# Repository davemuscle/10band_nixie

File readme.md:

# IN-9 Nixie Tube Spectrum Analyzer - Analog

*Migrated to Git on February 20th, 2022. Original release July 5th, 2020.*

I've been interested in doing a project with IN-9 Nixie Tubes for some time, and with the
manufacturing for these "old world" displays having been discontinued for decades now, it definitely
feels special to work with these devices. IN-9s are glass tubes filled with Neon or Argon gas, and
when driven by 150V and a low current is sunk through them, the tube lights up and looks nice. I
picked up 25 IN-9 Nixie Tubes for $130 from a Ukrainian seller on Ebay for this and future projects.

It seemed like these tubes just wanted to be used for a 10-band spectrum analyzer, so I decided to
make it completely analog to switch things up. It was fun building the filters, peak detectors, and
boost converter, and I'm happy with the result; but the next projects will be going back to digital,
for sure.

The general timeframe of this project was between mid-April to the end of May 2020. I also
redesigned the website at the start of July.

## Demonstration
CTRL+click the video thumbnails to open in a new tab

| Youtube Videos |
| :--: |
| *IN-9 Nixie Tube 10-Band Spectrum Analyzer - Demo* |
|  |
| *IN-9 Nixie Tube 10-Band Spectrum Analyzer - OSRS Lunar Isle* |
|  |

## Implementation

### Tube Operation

The general operation of the IN-9 is pretty simple, as there are only two pins to work with. When a
striking voltage of ~150V is placed on the anode of the device, the Neon / Argon gas in the tube
becomes ionized, converting it into plasma.

When a current is then sunk through the tube, the plasma sputters against the cathode to produce the
glow. The height of the glow is linearlly proportional to the current through the tube, up to 10 mA.
After that the glow just gets brighter.

### Tube Circuitry

The circuit I used to drive each IN-9 tube was a simple NPN current sink. The only hard part in
using these tubes is getting your hands on +150V. The power circuit is shown later in the
"Schematic" section.

In the circuit below, R1 and Vb control the current through the tube. 

Any NPN can be used as long as the Collector-Emmitter breakdown voltage is reasonably higher than
the striking voltage. I used an MJE340, which has a breakdown of 300V (double my striking voltage).

### Tube Burn-In

Each Nixie has to go through a "burn-in" process. This process is just driving the tube at a higher
current for any amount of time. To burn my tubes in I lowered R1 in the circuit above. Shown below
is a 4x speedup of a tube being slowly burned in.

Most of the tubes available for purchase are NOS: "new-old stock", meaning they are old but unused.
They need to be burned in because they've been sitting in a warehouse in Russia for 30 years!

Burn in can also fix issues related to cathode poisoning, which is the build-up of deposited metal
on the cathode from the sputtering mentioned earlier. Cathode poisoning can cause tubes to stop
working or be less visible.

### Tube Failures

The reliability of the tubes is definitely not a buying point. Out of the 15 I tested, 2 of them
wouldn't work correctly and 1 of them mysteriously stopped working.

The picture above was me trying to reburn-in the tube that had stopped working. That white
light highlited in red isn't from a camera; it's some failure by the tube. Either the neon wasn't
ionizing, this was cathode poisoning, or something else. 

You'll also notice in the demo videos that the right-most tube doesn't display correctly, which is
fine. 

## Schematic

[Download a PDF of the schematic here](/doc/NixieAnalyzer.pdf)

### Power

The Nixie Tubes are powered buy 12V boosted up to 150V using the MC34063 switching controller (for
an SMPS). This is an old, cheap, simple chip that can act as a boost / buck converter, or as a
voltage inverter. It works by adjusting the switching duty-cycle out of pin 2 to regulate a constant
output voltage. In my configuration, 12V gets boosted up to ~75V through Q2, L1 and C10. The
capacitor network on the output acts as a doubler, giving me ~150V.

I was actually able to build this SMPS on a breadboard, but make sure to pay attention to your
wiring if you decide to. I had to build it a few times to get it right. The only issue I experienced
was the voltage dropout on the load. With 5 tubes on at full height, the voltage dropped to about
~130V. This was because the MC34063 only has a max duty cycle of 85%; a modern chip with better
efficiency probably wouldn't have dropped out. 

Check the references for the source for this circuit.

I used the L7805 regulator to convert 12V to 5V for powering the OpAmps / other ICs.

### Audio Front End

The audio layer is just an input and output jack and an inverting amplifier. I like to make my
spectrum analyzer's not change the volume of the sound, so I just did a loopback here. The sound is
split from stereo to mono via R26 and R27, and is passed through an inverting amplifier. RV2 can be
turned to give a gain between 1 and 18. When soldering the circuit I used 300ohms for R31 and R34
since I wanted more gain.

Since I used a single-supply setup for my board, I had to generate a 2.5V bias using R32, R33, and
U7B. 

### State Variable Filter, Peak Detector, Current Sink (repeat 10x)

The bandpass filter topology I went with was the State Variable Filter. It's a good topology since
you only need to swap out two resistors, R13 and R15, to get a different center frequency. R6, R7,
and R9 control the gain and Q-factor, which I just played with to get right. R11 and R12 I picked 1K
and never had to change it. I believe those resistors cancel out in the reduced equations. 

Another good reason to use the State Variable Filter is that you also get lowpass and highpass
outputs. The highpass output is on pin 7, and the lowpass is on pin 14 of U3.

After filtering the sound through the bandpass filter, I convert it to DC via the peak detector at
U4. We have now effectively taken an FFT.

The DC peak then goes through a jumper and into the base of the NPN current sink. The jumper allows
for switching between burning the tube in or normal operation.

### Tube Driver

I extended the NPN current sink by adding an additional transistor at the emitter of the MJE340.
This transistor was driven by a pulse, about 100 Hz, making the current through the tube be pulsed.
This is required for using IN-9 tubes, otherwise they will not operate correctly: sometimes the glow
will start in the middle, or maybe the glow will extend from the top-down. The IN-13's tried to fix
this by adding an auxilliary cathode pin, but I'm not sure how well that works.

U6 is the common 555 timer, used to generate the 100 Hz pulse. You can use any frequency above the
persistence of version (see the references), I found 100 Hz to work well. D6 is used to get as close
to 50% duty cycle as possible.

The output of the 555 timer is then inverted via Q4, to give me two square waves (TubeClockA,
TubeClockB) with a 180 degree phase difference. TubeClockA enables to 5 tubes, and TubeClockB
enables 5 tubes, each at different times. This relaxes my power supply current by only having to
power 5 tubes at once. But, since the tubes are actually being flickered at 100 Hz, we perceive 10
of them as constantly on.

RV1 is a trim potentiometer used to vary the burn-in voltage. For my circuit, 3-4V was pretty good.

## Layout

The general layout is: audio layer and tube driver on the left, filters in the middle, power on the
right.

The bottom part of the PCB with the holes snaps off and fits on top of the main board. Rubber
grommets are inserted into the holes, the nixie tubes are pushed in, and their leads are snapped
into the screw terminals. I wanted a setup like this so I didn't have to solder any tubes onto the
board. Each tube can be easily swapped if there is a failure.

I included an extra two snap-off Nixie holders for future projects. The rubber grommets that
perfectly fit the IN-9s I used are the "742" from Keystone Electronics. They have a inner diameter
of 0.312", a panel thickness of 0.062", a cutout of 0.437", and a total diameter of 0.625". I had to
try a bunch of different grommets until I found the right one, so hopefully this is helpful.

## Improvements

A smarter way to do this would have been with a switched-capacitor filter, which would have reduced
soldering time and component count. I would remove the 32 Hz and 16 kHz bands, since those tubes are
hardly used compared to the others. I would also use a higher voltage than 5V for the main power
rail. Using 5V limited my headroom and dynamic range.

## References
1. [Wikipedia, Nixie Tubes](https://en.wikipedia.org/wiki/Nixie_tube)
2. [Wikipedia, Plasma](https://en.wikipedia.org/wiki/Plasma_physics)
3. [Wikipedia, Ionization](https://en.wikipedia.org/wiki/Ionization)
4. [Wikipedia, Sputtering](https://en.wikipedia.org/wiki/Sputtering)
5. [Threeneuron's, Nixie Power Supply](https://threeneurons.wordpress.com/nixie-power-supply/)
6. [SaltEChips, Theory of operation and construction of the IN-13 nixie gas-discharge
   tube](https://www.saltechips.com/lab/theory-of-operation-and-construction-of-the-in-13-nixie-gas-discharge-tube/)
7. [Dieter's Nixie-Tube Pages, Tutorial: Cathode Poisoning
   Reversal](http://www.tube-tester.com/sites/nixie/different/cathode%20poisoning/cathode-poisoning.htm)
8. [Good Nixie Discussion on GoogleGroups](https://groups.google.com/g/neonixie-l/c/GAREG0tdVsI)
9. [Driving IN-9 Neon Displays](https://www.die-wuestens.de/rd/IN9-2.pdf)

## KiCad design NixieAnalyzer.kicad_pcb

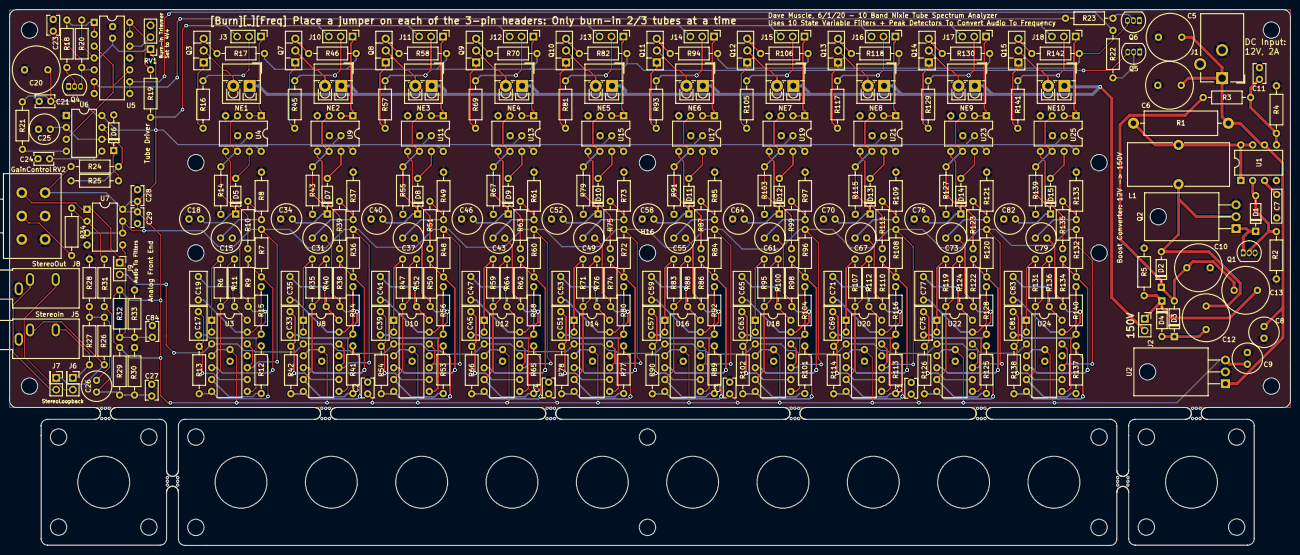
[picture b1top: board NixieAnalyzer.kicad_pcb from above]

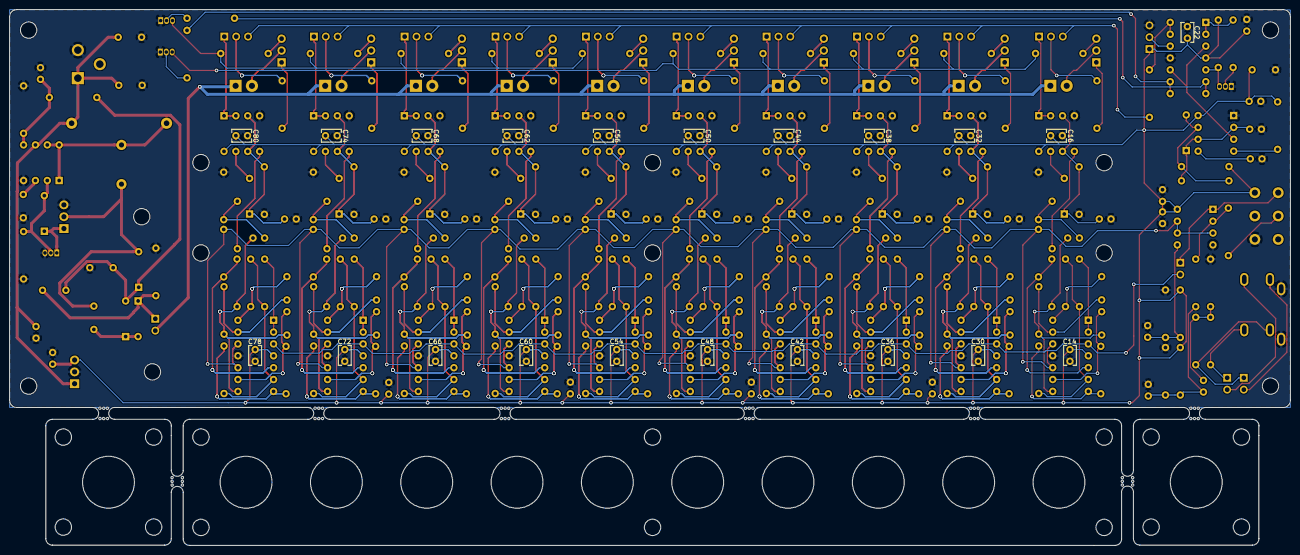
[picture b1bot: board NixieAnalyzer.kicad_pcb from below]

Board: 2 copper layers, 274.1 x 114.7 mm, 343 parts (21 on the bottom side), 212 nets.

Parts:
C1, C2, C3, C4, C23, C28: 1u; C_Rect_L4.0mm_W2.5mm_P2.50mm
C5, C10: 2.2u; C_Radial_D10.0mm_H16.0mm_P5.00mm
C6: 10u; C_Radial_D10.0mm_H16.0mm_P5.00mm
C7: 680p; C_Rect_L7.0mm_W2.0mm_P5.00mm
C8: 0.22u; C_Radial_D6.3mm_H7.0mm_P2.50mm
C9: 0.1u; C_Radial_D6.3mm_H7.0mm_P2.50mm
C11: 10n; C_Rect_L4.0mm_W2.5mm_P2.50mm
C12, C13: 10u; C_Radial_D10.0mm_H12.5mm_P5.00mm
C14, C16, C21, C22, C24, C27, C29, C30, C32, C36, C38, C42, C44, C48, C50, C54, C56, C60, C62, C66, C68, C72, C74, C78, C80, C84: 0.1u; C_Rect_L4.0mm_W2.5mm_P2.50mm
C15, C26, C31, C37, C43, C49, C55, C61, C67, C73, C79: 10u; C_Radial_D6.3mm_H7.0mm_P2.50mm
C17, C19, C33, C35, C39, C41, C45, C47, C51, C53, C57, C59, C63, C65, C69, C71, C75, C77, C81, C83: 0.1u; C_Rect_L7.0mm_W3.5mm_P5.00mm
C18, C25, C34, C40, C46, C52, C58, C64, C70, C76, C82: 1u; C_Radial_D6.3mm_H7.0mm_P2.50mm
C20: 220u; C_Radial_D10.0mm_H16.0mm_P5.00mm
D1, D5, D6, D7, D8, D9, D10, D11, D12, D13, D14, D15: 1N914; D_DO-35_SOD27_P7.62mm_Horizontal
D2, D3, D4: BAV21; D_DO-35_SOD27_P7.62mm_Horizontal
H1, H2, H3, H4: Board Edge Mounts; MountingHole_3.5mm
H5, H6, H7, H8, H9, H10, H11, H12, H13, H14, H15, H16, H17, H18, H19, H20, H21, H22, H23, H24: Nixie Board Mounts; MountingHole_3.5mm
J1: Barrel_Jack; BarrelJack_CUI_PJ-102AH_Horizontal
J2, J6, J7, J9: Conn_02x01; PinHeader_2x01_P2.54mm_Vertical
J3, J10, J11, J12, J13, J14, J15, J16, J17, J18: Conn_01x03; PinHeader_1x03_P2.54mm_Vertical
J5: InputStereo; Jack_3.5mm_CUI_SJ1-3533NG_Horizontal
J8: OutputStereo; Jack_3.5mm_CUI_SJ1-3533NG_Horizontal
L1: 220u; L_Toroid_Vertical_L21.6mm_W9.1mm_P8.40mm_Bourns_5700
NE1, NE2, NE3, NE4, NE5, NE6, NE7, NE8, NE9, NE10: IN-9; TerminalBlock_4Ucon_1x02_P3.50mm_Vertical
Q1: 2N3906; TO-92_Inline
Q2: IRF740A; TO-220-3_Horizontal_TabDown
Q3, Q7, Q8, Q9, Q10, Q11, Q12, Q13, Q14, Q15: MJE340; TO-126-3_Vertical
Q4, Q5, Q6: PN2222A; TO-92_Inline
R1: 0.1; R_Axial_DIN0516_L15.5mm_D5.0mm_P20.32mm_Horizontal
R2: 240; R_Axial_DIN0207_L6.3mm_D2.5mm_P10.16mm_Horizontal
R3: 220K; R_Axial_DIN0207_L6.3mm_D2.5mm_P10.16mm_Horizontal
R4: 3.6K; R_Axial_DIN0207_L6.3mm_D2.5mm_P10.16mm_Horizontal
R5: 1M Bleeder; R_Axial_DIN0207_L6.3mm_D2.5mm_P10.16mm_Horizontal
R6, R35, R47, R59, R71, R83, R95, R107, R119, R131: 1.5K; R_Axial_DIN0207_L6.3mm_D2.5mm_P10.16mm_Horizontal
R7, R8, R10, R25, R36, R37, R39, R48, R49, R51, R60, R61, R63, R72, R73, R75, R84, R85, R87, R96, R97, R99, R108, R109, R111, R120, R121, R123, R132, R133, R135: 10K; R_Axial_DIN0207_L6.3mm_D2.5mm_P10.16mm_Horizontal
R9, R38, R50, R62, R74, R86, R98, R110, R122, R134: 33K; R_Axial_DIN0207_L6.3mm_D2.5mm_P10.16mm_Horizontal
R11, R12, R16, R18, R21, R32, R33, R40, R41, R45, R52, R53, R57, R64, R65, R69, R76, R77, R81, R88, R89, R93, R100, R101, R105, R112, R113, R117, R124, R125, R129, R136, R137, R141: 1K; R_Axial_DIN0207_L6.3mm_D2.5mm_P10.16mm_Horizontal
R13, R15, R42, R44, R54, R56, R66, R68, R78, R80, R90, R92, R102, R104, R114, R116, R126, R128, R138, R140: RC; R_Axial_DIN0207_L6.3mm_D2.5mm_P10.16mm_Horizontal
R14, R43, R55, R67, R79, R91, R103, R115, R127, R139: 1M; R_Axial_DIN0207_L6.3mm_D2.5mm_P10.16mm_Horizontal
R17, R46, R58, R70, R82, R94, R106, R118, R130, R142: 100; R_Axial_DIN0207_L6.3mm_D2.5mm_P10.16mm_Horizontal
R19, R28: 56K; R_Axial_DIN0207_L6.3mm_D2.5mm_P10.16mm_Horizontal
R20, R22, R23: 5.6K; R_Axial_DIN0207_L6.3mm_D2.5mm_P10.16mm_Horizontal
R24: 8.2K; R_Axial_DIN0207_L6.3mm_D2.5mm_P10.16mm_Horizontal
R26, R27: 470; R_Axial_DIN0207_L6.3mm_D2.5mm_P10.16mm_Horizontal
R29, R30: 68K; R_Axial_DIN0207_L6.3mm_D2.5mm_P10.16mm_Horizontal
R31, R34: 600; R_Axial_DIN0207_L6.3mm_D2.5mm_P10.16mm_Horizontal
RV1: R_POT; PinHeader_1x03_P2.54mm_Vertical
RV2: 10K; Potentiometer_Alps_RK163_Dual_Horizontal
U1: MC34063AP; DIP-8_W7.62mm
U2: L7805; TO-220-3_Horizontal_TabDown
U3, U5, U8, U10, U12, U14, U16, U18, U20, U22, U24: MCP6004; DIP-14_W7.62mm
U4, U7, U9, U11, U13, U15, U17, U19, U21, U23, U25: MCP6002-xP; DIP-8_W7.62mm
U6: LM555; DIP-8_W7.62mm
mouse-bite-2.54mm-slot, mouse-bite-2.54mm-slot#2, mouse-bite-2.54mm-slot#3, mouse-bite-2.54mm-slot#4, mouse-bite-2.54mm-slot#5, mouse-bite-2.54mm-slot#6, mouse-bite-2.54mm-slot#7, mouse-bite-2.54mm-slot#8: VAL**; mouse-bite-2.54mm-slot

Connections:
5V: C1.1, C2.1, C3.1, C4.1, C9.1, C14.1, C16.2, C20.1, C21.1, C22.1, C23.2, C28.2, C29.2, C30.1, C32.2, C36.1, C38.2, C42.1, C44.2, C48.1, C50.2, C54.1, C56.2, C60.1, C62.2, C66.1, C68.2, C72.1, C74.2, C78.1, C80.2, R20.1, R21.2, R24.1, R29.2, R32.1, RV1.1, RV2.4, U2.3, U3.4, U4.8, U5.4, U6.8, U7.8, U8.4, U9.8, U10.4, U11.8, U12.4, U13.8, U14.4, U15.8, U16.4, U17.8, U18.4, U19.8, U20.4, U21.8, U22.4, U23.8, U24.4, U25.8
150V: J2.2, NE1.1, NE2.1, NE3.1, NE4.1, NE5.1, NE6.1, NE7.1, NE8.1, NE9.1, NE10.1
+12V: C5.1, C6.1, C8.1, J1.1, R1.1, U1.6, U2.1
/Sheet5ECF3EB8/Bandpass: C15.2, C17.1, R9.2, R15.1, U3.8
/Sheet5ECF3EB8/PeakDetect: J3.1, U4.1, U4.2
/Sheet5ECF3EB8/TubeCommon: Q5.3, R17.2, R46.2, R58.2, R70.2, R82.2
/Sheet5ECF3EB8/TubeValue: J3.2, R16.2
/Sheet5EEA538E/TubeClockA: R22.2, U5.8, U5.9
/Sheet5EEA538E/TubeClockB: R23.1, U5.6, U5.7
/Sheet5EEA538E/fosc: U5.3, U5.10, U6.3
/sheet5EF34C22/Bandpass: C49.2, C51.1, R74.2, R80.1, U14.8
/sheet5EF34C22/PeakDetect: J13.1, U15.1, U15.2
/sheet5EF34C22/TubeValue: J13.2, R81.2
/sheet5EF34C23/Bandpass: C55.2, C57.1, R86.2, R92.1, U16.8
/sheet5EF34C23/PeakDetect: J14.1, U17.1, U17.2
/sheet5EF34C23/TubeCommon: Q6.3, R94.2, R106.2, R118.2, R130.2, R142.2
/sheet5EF34C23/TubeValue: J14.2, R93.2
/sheet5EF34C24/Bandpass: C61.2, C63.1, R98.2, R104.1, U18.8
/sheet5EF34C24/PeakDetect: J15.1, U19.1, U19.2
/sheet5EF34C24/TubeValue: J15.2, R105.2
/sheet5EF34C25/Bandpass: C67.2, C69.1, R110.2, R116.1, U20.8
/sheet5EF34C25/PeakDetect: J16.1, U21.1, U21.2
/sheet5EF34C25/TubeValue: J16.2, R117.2
/sheet5EF342EE/Bandpass: C31.2, C33.1, R38.2, R44.1, U8.8
/sheet5EF342EE/PeakDetect: J10.1, U9.1, U9.2
/sheet5EF342EE/TubeValue: J10.2, R45.2
/sheet5EF345AE/Bandpass: C37.2, C39.1, R50.2, R56.1, U10.8
/sheet5EF345AE/PeakDetect: J11.1, U11.1, U11.2
/sheet5EF345AE/TubeValue: J11.2, R57.2
/sheet5EF345AF/Bandpass: C43.2, C45.1, R62.2, R68.1, U12.8
/sheet5EF345AF/PeakDetect: J12.1, U13.1, U13.2
/sheet5EF345AF/TubeValue: J12.2, R69.2
/sheet5EF3670A/Bandpass: C73.2, C75.1, R122.2, R128.1, U22.8
/sheet5EF3670A/PeakDetect: J17.1, U23.1, U23.2
/sheet5EF3670A/TubeValue: J17.2, R129.2
/sheet5EF3670B/Bandpass: C79.2, C81.1, R134.2, R140.1, U24.8
/sheet5EF3670B/PeakDetect: J18.1, U25.1, U25.2
/sheet5EF3670B/TubeValue: J18.2, R141.2
AudioIn: J9.2, U3.3, U8.3, U10.3, U12.3, U14.3, U16.3, U18.3, U20.3, U22.3, U24.3
GND: C1.2, C2.2, C3.2, C4.2, C5.2, C6.2, C7.2, C8.2, C9.2, C10.2, C11.2, C14.2, C16.1, C18.2, C20.2, C21.2, C22.2, C23.1, C24.2, C25.2, C27.1, C28.1, C29.1, C30.2, C32.1, C34.2, C36.2, C38.1, C40.2, C42.2, C44.1, C46.2, C48.2, C50.1, C52.2, C54.2, C56.1, C58.2, C60.2, C62.1, C64.2, C66.2, C68.1, C70.2, C72.2, C74.1, C76.2, C78.2, C80.1, C82.2, C84.1, J1.2, J5.S, J8.S, Q1.3, Q2.3, Q4.1, Q5.1, Q6.1, R2.2, R4.2, R5.2, R8.2, R14.1, R28.2, R30.1, R33.2, R37.2, R43.1, R49.2, R55.1, R61.2, R67.1, R73.2, R79.1, R85.2, R91.1, R97.2, R103.1, R109.2, R115.1, R121.2, R127.1, R133.2, R139.1, RV1.3, RV2.6, U1.4, U2.2, U3.11, U4.4, U5.11, U6.1, U7.4, U8.11, U9.4, U10.11, U11.4, U12.11, U13.4, U14.11, U15.4, U16.11, U17.4, U18.11, U19.4, U20.11, U21.4, U22.11, U23.4, U24.11, U25.4
unnamed: C7.1, U1.3
unnamed: C10.1, C13.2, D2.1, D3.2, R3.2
unnamed: C11.1, R3.1, R4.1, U1.5
unnamed: C12.1, D3.1, D4.2
unnamed: C12.2, D2.2, L1.2, Q2.2
unnamed: C13.1, D4.1, J2.1, R5.1
unnamed: C15.1, R8.1, R10.1
unnamed: C17.2, R13.2, U3.9
unnamed: C18.1, D5.1, R14.2, U4.3, U4.6
unnamed: C19.1, R11.2, U3.14
unnamed: C19.2, R15.2, U3.13
unnamed: C24.1, U6.5
unnamed: C25.1, D6.1, R25.2, U6.2, U6.6
unnamed: C26.1, C27.2, R29.1, R30.2, R31.2
unnamed: C26.2, R26.1, R27.1, R28.1
unnamed: C31.1, R37.1, R39.1
unnamed: C33.2, R42.2, U8.9
unnamed: C34.1, D7.1, R43.2, U9.3, U9.6
unnamed: C35.1, R40.2, U8.14
unnamed: C35.2, R44.2, U8.13
unnamed: C37.1, R49.1, R51.1
unnamed: C39.2, R54.2, U10.9
unnamed: C40.1, D8.1, R55.2, U11.3, U11.6
unnamed: C41.1, R52.2, U10.14
unnamed: C41.2, R56.2, U10.13
unnamed: C43.1, R61.1, R63.1
unnamed: C45.2, R66.2, U12.9
unnamed: C46.1, D9.1, R67.2, U13.3, U13.6
unnamed: C47.1, R64.2, U12.14
unnamed: C47.2, R68.2, U12.13
unnamed: C49.1, R73.1, R75.1
unnamed: C51.2, R78.2, U14.9
unnamed: C52.1, D10.1, R79.2, U15.3, U15.6
unnamed: C53.1, R76.2, U14.14
unnamed: C53.2, R80.2, U14.13
unnamed: C55.1, R85.1, R87.1
unnamed: C57.2, R90.2, U16.9
unnamed: C58.1, D11.1, R91.2, U17.3, U17.6
unnamed: C59.1, R88.2, U16.14
unnamed: C59.2, R92.2, U16.13
unnamed: C61.1, R97.1, R99.1
unnamed: C63.2, R102.2, U18.9
unnamed: C64.1, D12.1, R103.2, U19.3, U19.6
unnamed: C65.1, R100.2, U18.14
unnamed: C65.2, R104.2, U18.13
unnamed: C67.1, R109.1, R111.1
unnamed: C69.2, R114.2, U20.9
unnamed: C70.1, D13.1, R115.2, U21.3, U21.6
unnamed: C71.1, R112.2, U20.14
unnamed: C71.2, R116.2, U20.13
unnamed: C73.1, R121.1, R123.1
unnamed: C75.2, R126.2, U22.9
unnamed: C76.1, D14.1, R127.2, U23.3, U23.6
unnamed: C77.1, R124.2, U22.14
unnamed: C77.2, R128.2, U22.13
unnamed: C79.1, R133.1, R135.1
unnamed: C81.2, R138.2, U24.9
unnamed: C82.1, D15.1, R139.2, U25.3, U25.6
unnamed: C83.1, R136.2, U24.14
unnamed: C83.2, R140.2, U24.13
unnamed: C84.2, R32.2, R33.1, U7.5
unnamed: D1.1, Q1.1, Q2.1
unnamed: D1.2, Q1.2, R2.1, U1.2
unnamed: D5.2, U4.7
unnamed: D6.2, R24.2, R25.1, U6.7
unnamed: D7.2, U9.7
unnamed: D8.2, U11.7
unnamed: D9.2, U13.7
unnamed: D10.2, U15.7
unnamed: D11.2, U17.7
unnamed: D12.2, U19.7
unnamed: D13.2, U21.7
unnamed: D14.2, U23.7
unnamed: D15.2, U25.7
unnamed: J5.R, J6.1, R27.2
unnamed: J5.T, J7.1, R26.2
unnamed: J6.2, J8.R
unnamed: J7.2, J8.T
unnamed: J9.1, RV2.1, U7.1
unnamed: L1.1, R1.2, U1.1, U1.7, U1.8
unnamed: NE1.2, Q3.2
unnamed: NE2.2, Q7.2
unnamed: NE3.2, Q8.2
unnamed: NE4.2, Q9.2
unnamed: NE5.2, Q10.2
unnamed: NE6.2, Q11.2
unnamed: NE7.2, Q12.2
unnamed: NE8.2, Q13.2
unnamed: NE9.2, Q14.2
unnamed: NE10.2, Q15.2
unnamed: Q3.1, R16.1
unnamed: Q3.3, R17.1
unnamed: Q4.2, R18.2
unnamed: Q4.3, R20.2, U5.5
unnamed: Q5.2, R22.1
unnamed: Q6.2, R23.2
unnamed: Q7.1, R45.1
unnamed: Q7.3, R46.1
unnamed: Q8.1, R57.1
unnamed: Q8.3, R58.1
unnamed: Q9.1, R69.1
unnamed: Q9.3, R70.1
unnamed: Q10.1, R81.1
unnamed: Q10.3, R82.1
unnamed: Q11.1, R93.1
unnamed: Q11.3, R94.1
unnamed: Q12.1, R105.1
unnamed: Q12.3, R106.1
unnamed: Q13.1, R117.1
unnamed: Q13.3, R118.1
unnamed: Q14.1, R129.1
unnamed: Q14.3, R130.1
unnamed: Q15.1, R141.1
unnamed: Q15.3, R142.1
unnamed: R6.2, U3.1, U3.2
unnamed: R7.1, R9.1, U3.5
unnamed: R10.2, U4.5
unnamed: R6.1, R11.1, R12.1, U3.6
unnamed: R12.2, R13.1, U3.7
unnamed: R18.1, U5.1, U5.2
unnamed: R19.1, U5.13, U5.14
unnamed: R21.1, U6.4
unnamed: R31.1, R34.2, U7.2
unnamed: R34.1, RV2.2
unnamed: R35.1, R40.1, R41.1, U8.6
unnamed: R35.2, U8.1, U8.2
unnamed: R36.1, R38.1, U8.5
unnamed: R39.2, U9.5
unnamed: R41.2, R42.1, U8.7
unnamed: R47.1, R52.1, R53.1, U10.6
unnamed: R47.2, U10.1, U10.2
unnamed: R48.1, R50.1, U10.5
unnamed: R51.2, U11.5
unnamed: R53.2, R54.1, U10.7
unnamed: R59.1, R64.1, R65.1, U12.6
unnamed: R59.2, U12.1, U12.2
unnamed: R60.1, R62.1, U12.5
unnamed: R63.2, U13.5
unnamed: R65.2, R66.1, U12.7
unnamed: R71.1, R76.1, R77.1, U14.6
unnamed: R71.2, U14.1, U14.2
unnamed: R72.1, R74.1, U14.5
unnamed: R75.2, U15.5
unnamed: R77.2, R78.1, U14.7
unnamed: R83.1, R88.1, R89.1, U16.6
unnamed: R83.2, U16.1, U16.2
unnamed: R84.1, R86.1, U16.5
unnamed: R87.2, U17.5
unnamed: R89.2, R90.1, U16.7
unnamed: R95.2, U18.1, U18.2
unnamed: R96.1, R98.1, U18.5
unnamed: R99.2, U19.5
unnamed: R95.1, R100.1, R101.1, U18.6
unnamed: R101.2, R102.1, U18.7
unnamed: R107.1, R112.1, R113.1, U20.6
unnamed: R107.2, U20.1, U20.2
unnamed: R108.1, R110.1, U20.5
unnamed: R111.2, U21.5
unnamed: R113.2, R114.1, U20.7
unnamed: R119.1, R124.1, R125.1, U22.6
unnamed: R119.2, U22.1, U22.2
unnamed: R120.1, R122.1, U22.5
unnamed: R123.2, U23.5
unnamed: R125.2, R126.1, U22.7
unnamed: R131.1, R136.1, R137.1, U24.6
unnamed: R131.2, U24.1, U24.2
unnamed: R132.1, R134.1, U24.5
unnamed: R135.2, U25.5
unnamed: R137.2, R138.1, U24.7
unnamed: RV1.2, U5.12
Vbias: R7.2, R36.2, R48.2, R60.2, R72.2, R84.2, R96.2, R108.2, R120.2, R132.2, U3.10, U3.12, U7.3, U7.6, U7.7, U8.10, U8.12, U10.10, U10.12, U12.10, U12.12, U14.10, U14.12, U16.10, U16.12, U18.10, U18.12, U20.10, U20.12, U22.10, U22.12, U24.10, U24.12
Vburn: J3.3, J10.3, J11.3, J12.3, J13.3, J14.3, J15.3, J16.3, J17.3, J18.3, R19.2

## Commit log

2022-02-20 migrate to git
2022-02-20 added ltspice, added screenshots, moved kicad files under kicad folder, update readme
2022-02-20 fix hyphen
